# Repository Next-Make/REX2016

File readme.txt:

To get temperature in degC, take the value of the binary number on the LED display and divide by 10.

<Front Top of PCB>
__________________________________________________________________________
| LED10 | LED9  | LED8  | LED7 | LED6 | LED5 | LED4 | LED3 | LED2 | LED1 |
| = 512 | = 256 | = 128 | = 64 | = 32 | = 16 | = 8  | = 4  | = 2  | = 1  |
‾‾‾‾‾‾‾‾‾‾‾‾‾‾‾‾‾‾‾‾‾‾‾‾‾‾‾‾‾‾‾‾‾‾‾‾‾‾‾‾‾‾‾‾‾‾‾‾‾‾‾‾‾‾‾‾‾‾‾‾‾‾‾‾‾‾‾‾‾‾‾‾‾‾
<Front Bottom of PCB>

So if LED9 and LED6 are on, the value = 265 + 32, and the temperature = (265 + 64)/10.
Which results in 29.7degC.

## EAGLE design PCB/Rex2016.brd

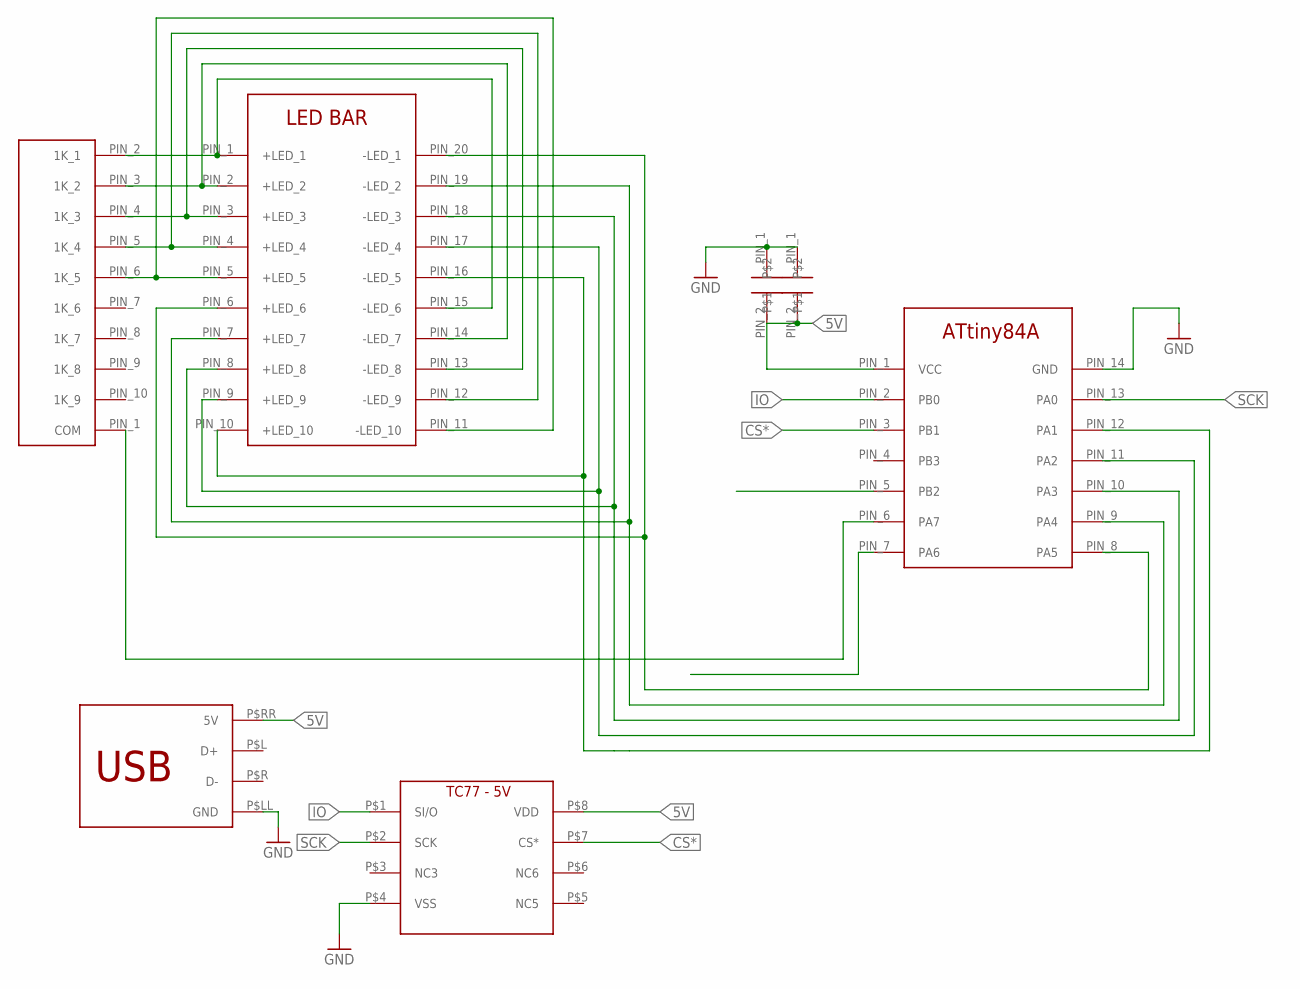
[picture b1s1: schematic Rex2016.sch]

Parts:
U$1: 9X_1K_BUSSED_R; SIP-10
U$2, U$6: 10UF_FK18; CAP_FK18
U$3: ATTINY84A; PDIP-14
U$4: LED_X10_BAR
U$5: TC77; SOIC-8
U$7: USB_A_TH

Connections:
5V: U$2.PIN_2, U$3.PIN_1 (VCC), U$5.P$8 (VDD), U$6.PIN_2, U$7.P$RR (5V)
CS*: U$3.PIN_3 (PB1), U$5.P$7 (CS*)
GND: U$2.PIN_1, U$3.PIN_14 (GND), U$5.P$4 (VSS), U$6.PIN_1, U$7.P$LL (GND)
IO: U$3.PIN_2 (PB0), U$5.P$1 (SI/O)
unnamed: U$1.PIN_2 (1K_1), U$4.PIN_1 (+LED_1), U$4.PIN_15 (-LED_6)
unnamed: U$1.PIN_3 (1K_2), U$4.PIN_2 (+LED_2), U$4.PIN_14 (-LED_7)
unnamed: U$1.PIN_4 (1K_3), U$4.PIN_3 (+LED_3), U$4.PIN_13 (-LED_8)
unnamed: U$1.PIN_5 (1K_4), U$4.PIN_4 (+LED_4), U$4.PIN_12 (-LED_9)
unnamed: U$1.PIN_6 (1K_5), U$4.PIN_5 (+LED_5), U$4.PIN_11 (-LED_10)
unnamed: U$3.PIN_12 (PA1), U$4.PIN_10 (+LED_10), U$4.PIN_16 (-LED_5)
unnamed: U$3.PIN_11 (PA2), U$4.PIN_9 (+LED_9), U$4.PIN_17 (-LED_4)
unnamed: U$3.PIN_10 (PA3), U$4.PIN_8 (+LED_8), U$4.PIN_18 (-LED_3)
unnamed: U$1.PIN_1 (COM), U$3.PIN_6 (PA7)
unnamed: U$3.PIN_9 (PA4), U$4.PIN_7 (+LED_7), U$4.PIN_19 (-LED_2)
unnamed: U$3.PIN_8 (PA5), U$4.PIN_6 (+LED_6), U$4.PIN_20 (-LED_1)
SCK: U$3.PIN_13 (PA0), U$5.P$2 (SCK)

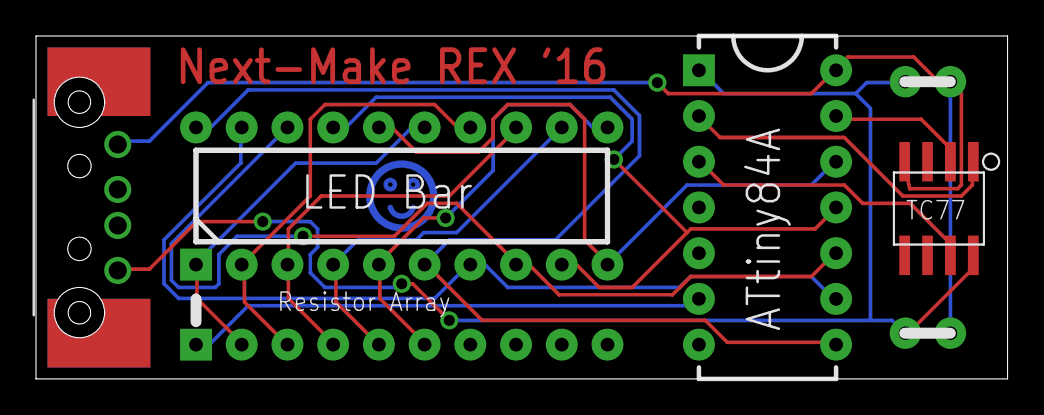
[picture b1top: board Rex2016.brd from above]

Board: 2 copper layers, 54.0 x 19.1 mm, 7 parts (0 on the bottom side), 16 nets.

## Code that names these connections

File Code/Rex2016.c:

/*
 * Rex2016.c
 *
 * Created: 7/18/2016 9:11:57 PM
 *  Author: sanoj737
 */ 


#include <avr/io.h>
#define F_CPU 8000000
#include <util/delay.h>

//OLD
//PA0 clock line to temp sensor
//PA1 chip select to temp sensor
//PA2 n/a
//PA3 LED resistor array
//PA4 n/a
//PA5 6th LED, also 1st LED
//PA6 7th LED, also 2nd LED
//PA7 8th LED, also 3rd LED
//PB0 I/O line to temp sensor
//PB1 9th LED, also 4th LED
//PB2 10th LED, also 5th LED

//NEW
//PA0 clock line to temp sensor
//PA1 1st LED, also 6th LED
//PA2 2nd LED, also 7th LED
//PA3 3rd LED, also 8th LED
//PA4 4th LED, also 9th LED
//PA5 5th LED, also 10th LED
//PA6 n/a
//PA7 LED resistor array
//PB0 I/O line to temp sensor
//PB1 chip select line to temp sensor
//PB2 n/a
//PB3 n/a

// num is a number from 0 to 1023
int numDisplay = 0;
char smallerHalf = 0;
void displayAsBinary(void)
{
	//create copy of ports to avoid flickering
	int tempA = PORTA;
	
	//make a copy of number so we don't modify it
	int num = numDisplay;
	
	if(!smallerHalf)
	{
		//set all outputs high
		tempA |= 0b10111110;
		
		if(num >= 512)
		{
			//turn on the 10th LED
			tempA &= ~(1 << 5);
			num = num - 512;
		}
		if(num >= 256)
		{
			//turn on 9th LED
			tempA &= ~(1 << 4);
			num = num - 256;
		}
		if(num >= 128)
		{
			//turn on 8th LED
			tempA &= ~(1 << 3);
			num = num - 128;
		}
		if(num >= 64)
		{
			//turn on 7th LED
			tempA &= ~(1 << 2);
			num = num - 64;
		}
		if(num >= 32)
		{
			//turn on 6th LED
			tempA &= ~(1 << 1);
			num = num - 32;
		}
	}
	
	else
	{
		//remove part of number greater than 32
		num = num%32;
		
		//set all outputs low
		tempA &= 0b01000001;
		
		if(num >= 16)
		{
			//turn on 5th LED
			tempA |= (1 << 5);
			num = num - 16;
		}
		if(num >= 8)
		{
			//turn on 4th LED
			tempA |= (1 << 4);
			num = num - 8;
		}
		if(num >= 4)
		{
			//turn on 3rd LED
			tempA |= (1 << 3);
			num = num - 4;
		}
		if(num >= 2)
		{
			//turn on 2nd LED
			tempA |= (1 << 2);
			num = num - 2;
		}
		if(num >= 1)
		{
			//turn on 1st LED
			tempA |= (1 << 1);
			num = num - 1;
		}
	}
	
	
	//set to outputs
	PORTA = tempA;
	
	//display other half next cycle
	smallerHalf = 1-smallerHalf;
}

long sensorValue = 0;
long tempInCentiC = 0;
void readSensor(void)
{
	//set clock line low
	PORTA &= 0b11111110;
	_delay_us(10);
	
	//set CS pin low
	PORTB &= 0b11111101;
	_delay_us(100);
	
	
	char neg = 0;
	
	sensorValue = 0;
	
	//clock in data to uC from temp sensor
	for(int a=0; a<16; a++)
	{
		PORTA |= 0b00000001;
		_delay_us(10);
		
		
		if((a==0) | (a==1) | (a==2))
		{
			neg = (PINB & (1<<0));
		}
		//else if(a==1)
		//{
		//do nothing
		//	;
		//}
		else if(a<13)
		{
			sensorValue = sensorValue + (1<<(12-a))*(PINB & (1<<0));
			//sensorValue += (PINB & (1<<0));
		}
		
		PORTA &= 0b11111110;
		_delay_us(10);
		
	}
	tempInCentiC = sensorValue*125*10/2000;
	//if(neg == 1)
	//{
	//	sensorValue = 0;
	//}
	
	//set CS pin high
	PORTB |= 0b00000010;
}

int main(void)
{
	// These set whether our pins are input (0) or output (1) for port A and B
	DDRA = 0b11111111;
	DDRB = 0b11111110;
	
	//initially set all pins low
	PORTA &= 0b00000000;
	PORTB &= 0b00000010;
	//initially set CS pin high
	PORTB |= 0b00000010;
	
	int temp = 0;
	int temp2 = 0;
	//while(1)
	//{
	//	numDisplay = 0b1010101010;
	//	displayAsBinary();
	//	_delay_us(1000);
	//}
	while(1)
	{
		temp += 1;
		if((temp%500) == 0)
		{
			temp = 0;
			//numDisplay += 1;
			//numDisplay = numDisplay%1023;
			//read temp twice per second
			readSensor();
		}
		
		temp2 += 1;
		if((temp%50) == 0)
		{
			temp2 = 0;
			if(numDisplay<tempInCentiC)
			{
				numDisplay += 1;
			}
			if(numDisplay>tempInCentiC)
			{
				numDisplay -= 1;
			}
		}
		
		displayAsBinary();
		
		_delay_us(1000);
	}
	
}

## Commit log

2016-08-31 Added Files
2016-08-31 Added other things
